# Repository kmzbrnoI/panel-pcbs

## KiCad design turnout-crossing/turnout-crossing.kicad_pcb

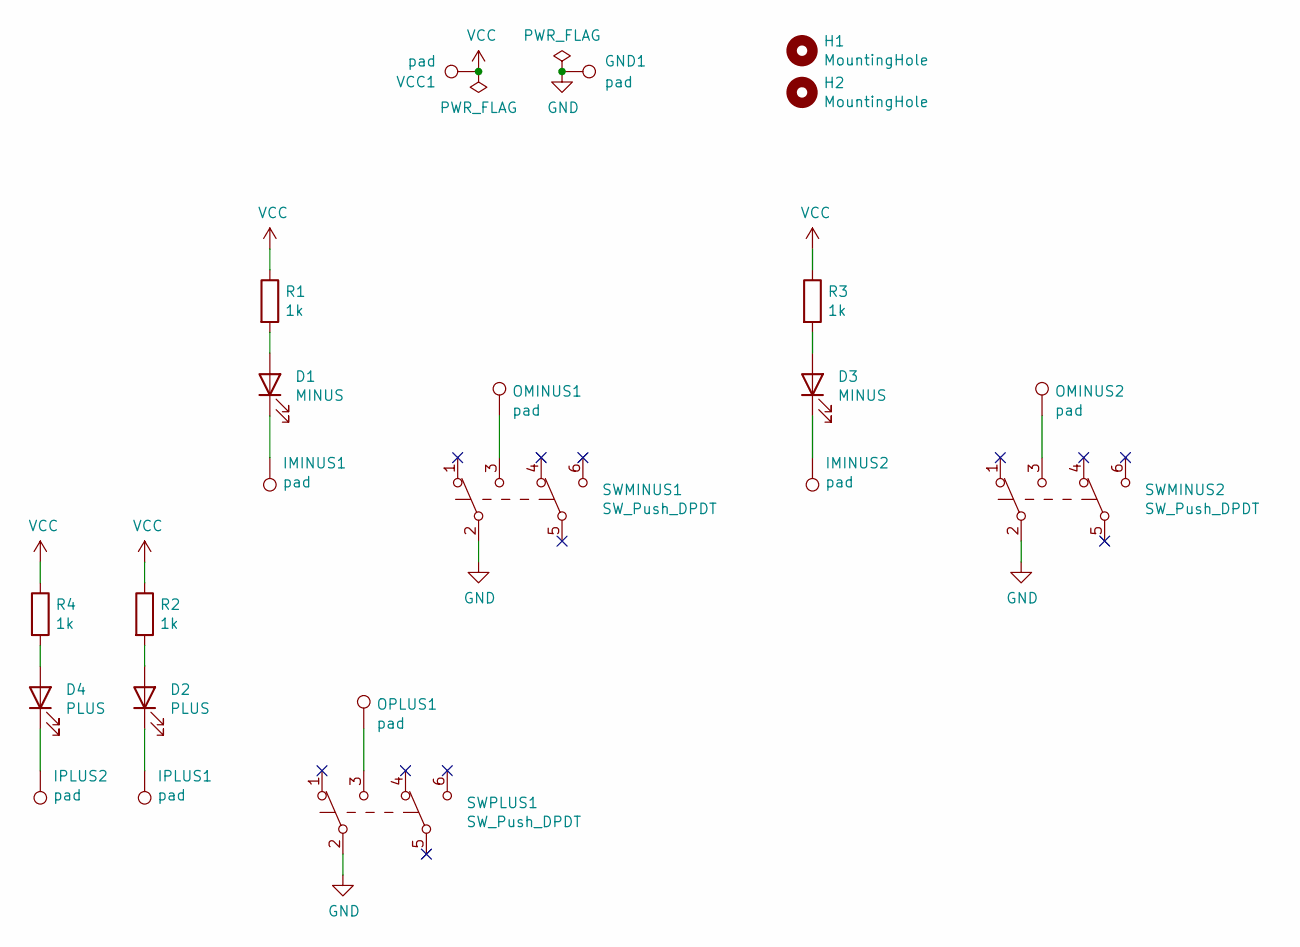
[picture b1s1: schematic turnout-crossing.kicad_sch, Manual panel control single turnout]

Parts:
D1, D3: MINUS; LED_D3.0mm
D2, D4: PLUS; LED_D3.0mm
GND1: pad; Pin_D1.3mm_L11.0mm
H1, H2: MountingHole; MountingHole_3.2mm_M3
IMINUS1, IMINUS2: pad; Pin_D1.3mm_L11.0mm
IPLUS1, IPLUS2: pad; Pin_D1.3mm_L11.0mm
OMINUS1, OMINUS2: pad; Pin_D1.3mm_L11.0mm
OPLUS1: pad; Pin_D1.3mm_L11.0mm
R1, R2, R3, R4: 1k; R_0805_2012Metric_Pad1.20x1.40mm_HandSolder
SWMINUS1, SWMINUS2: SW_Push_DPDT; KLS7
SWPLUS1: SW_Push_DPDT; KLS7
VCC1: pad; Pin_D1.3mm_L11.0mm

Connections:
GND: GND1.1, SWMINUS1.2 (B), SWMINUS2.2 (B), SWPLUS1.2 (B)
unnamed: D1.1 (K), IMINUS1.1
unnamed: D1.2 (A), R1.2
unnamed: D2.1 (K), IPLUS1.1
unnamed: D2.2 (A), R2.2
unnamed: D3.1 (K), IMINUS2.1
unnamed: D3.2 (A), R3.2
unnamed: D4.1 (K), IPLUS2.1
unnamed: D4.2 (A), R4.2
unnamed: OMINUS1.1, SWMINUS1.3 (C)
unnamed: OMINUS2.1, SWMINUS2.3 (C)
unnamed: OPLUS1.1, SWPLUS1.3 (C)
VCC: R1.1, R2.1, R3.1, R4.1, VCC1.1

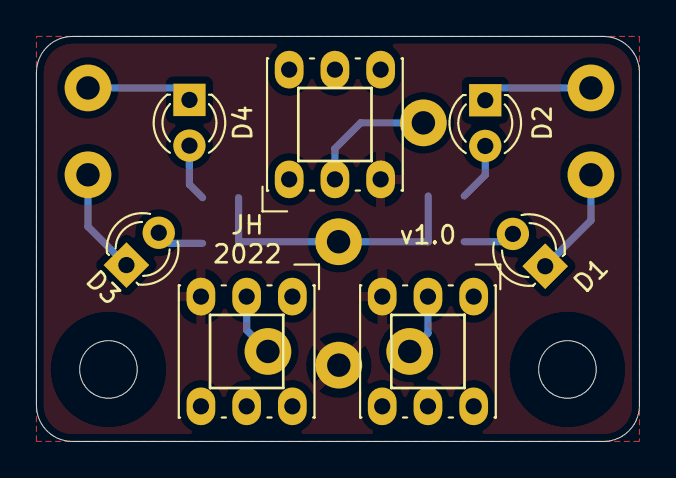
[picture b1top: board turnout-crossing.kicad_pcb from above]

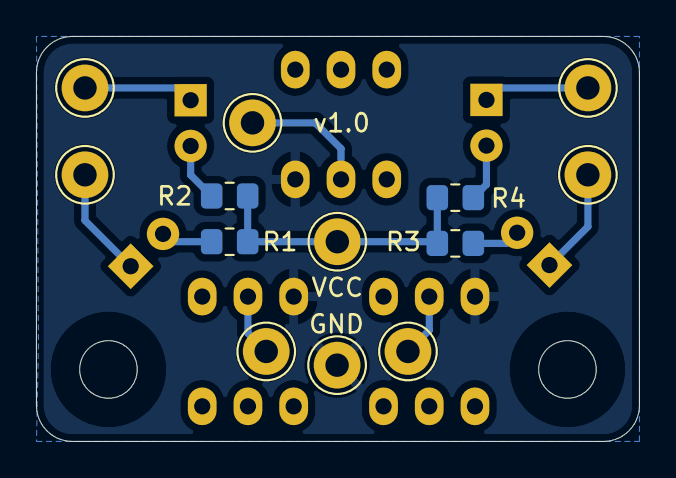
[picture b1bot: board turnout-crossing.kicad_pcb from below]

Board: 2 copper layers, 33.5 x 22.5 mm, 22 parts (13 on the bottom side), 13 nets.

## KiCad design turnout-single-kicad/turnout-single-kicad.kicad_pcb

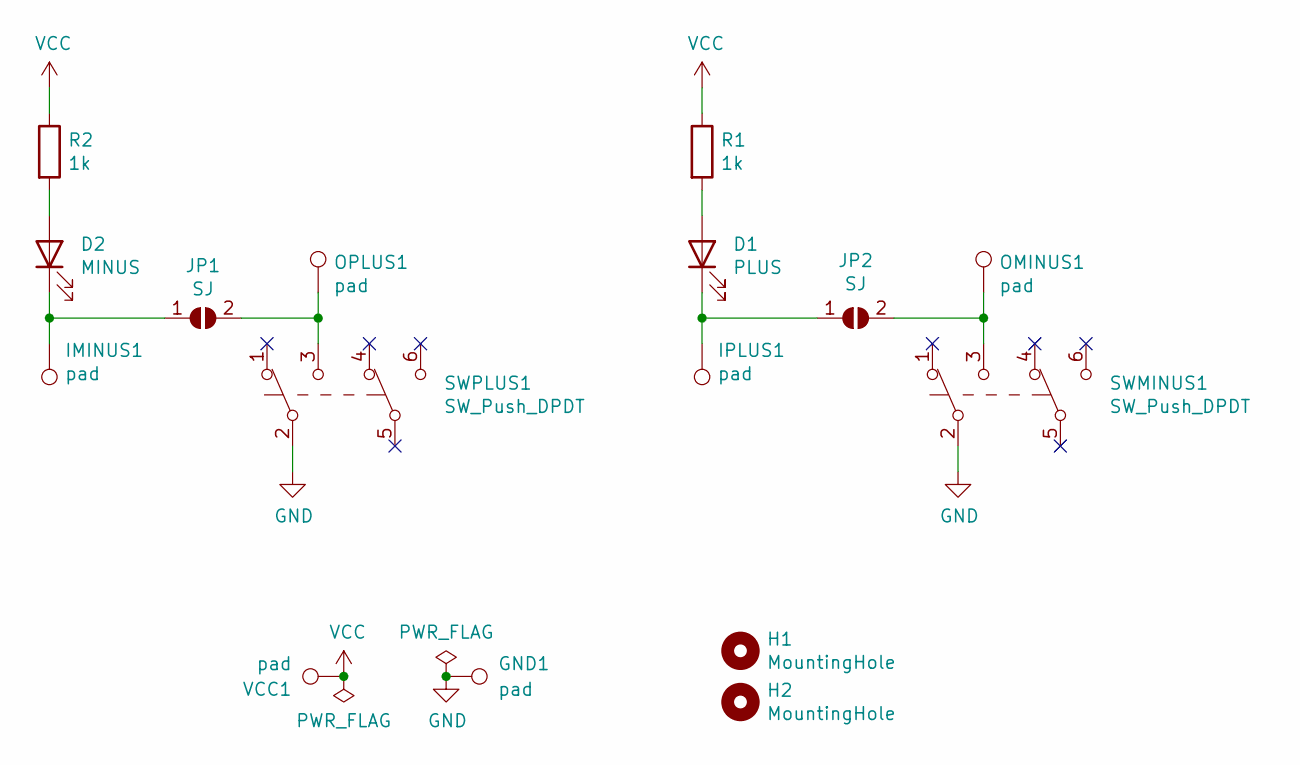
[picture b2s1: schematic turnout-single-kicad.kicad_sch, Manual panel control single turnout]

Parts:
D1: PLUS; LED_D3.0mm
D2: MINUS; LED_D3.0mm
GND1: pad; Pin_D1.3mm_L11.0mm
H1, H2: MountingHole; MountingHole_3.2mm_M3
IMINUS1: pad; Pin_D1.3mm_L11.0mm
IPLUS1: pad; Pin_D1.3mm_L11.0mm
JP1, JP2: SJ; SolderJumper-2_P1.3mm_Open_RoundedPad1.0x1.5mm
OMINUS1: pad; Pin_D1.3mm_L11.0mm
OPLUS1: pad; Pin_D1.3mm_L11.0mm
R1, R2: 1k; R_0805_2012Metric_Pad1.20x1.40mm_HandSolder
SWMINUS1: SW_Push_DPDT; KLS7
SWPLUS1: SW_Push_DPDT; KLS7
VCC1: pad; Pin_D1.3mm_L11.0mm

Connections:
GND: GND1.1, SWMINUS1.2 (B), SWPLUS1.2 (B)
unnamed: D1.1 (K), IPLUS1.1, JP2.1 (A)
unnamed: D1.2 (A), R1.2
unnamed: D2.1 (K), IMINUS1.1, JP1.1 (A)
unnamed: D2.2 (A), R2.2
unnamed: JP1.2 (B), OPLUS1.1, SWPLUS1.3 (C)
unnamed: JP2.2 (B), OMINUS1.1, SWMINUS1.3 (C)
VCC: R1.1, R2.1, VCC1.1

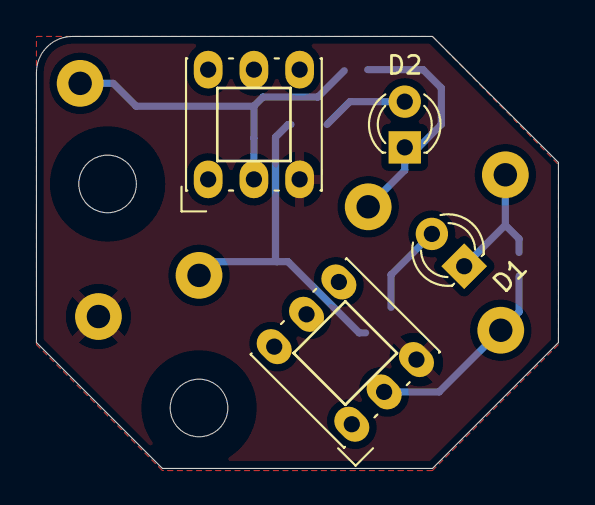
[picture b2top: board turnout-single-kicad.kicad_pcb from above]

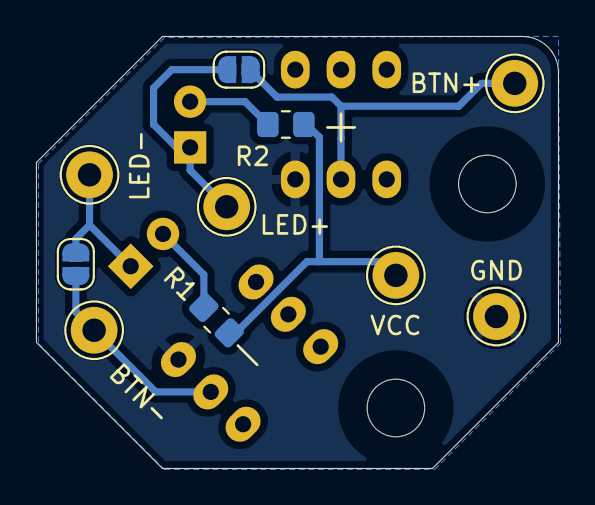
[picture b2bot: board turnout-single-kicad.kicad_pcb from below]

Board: 2 copper layers, 29.0 x 24.0 mm, 16 parts (10 on the bottom side), 8 nets.

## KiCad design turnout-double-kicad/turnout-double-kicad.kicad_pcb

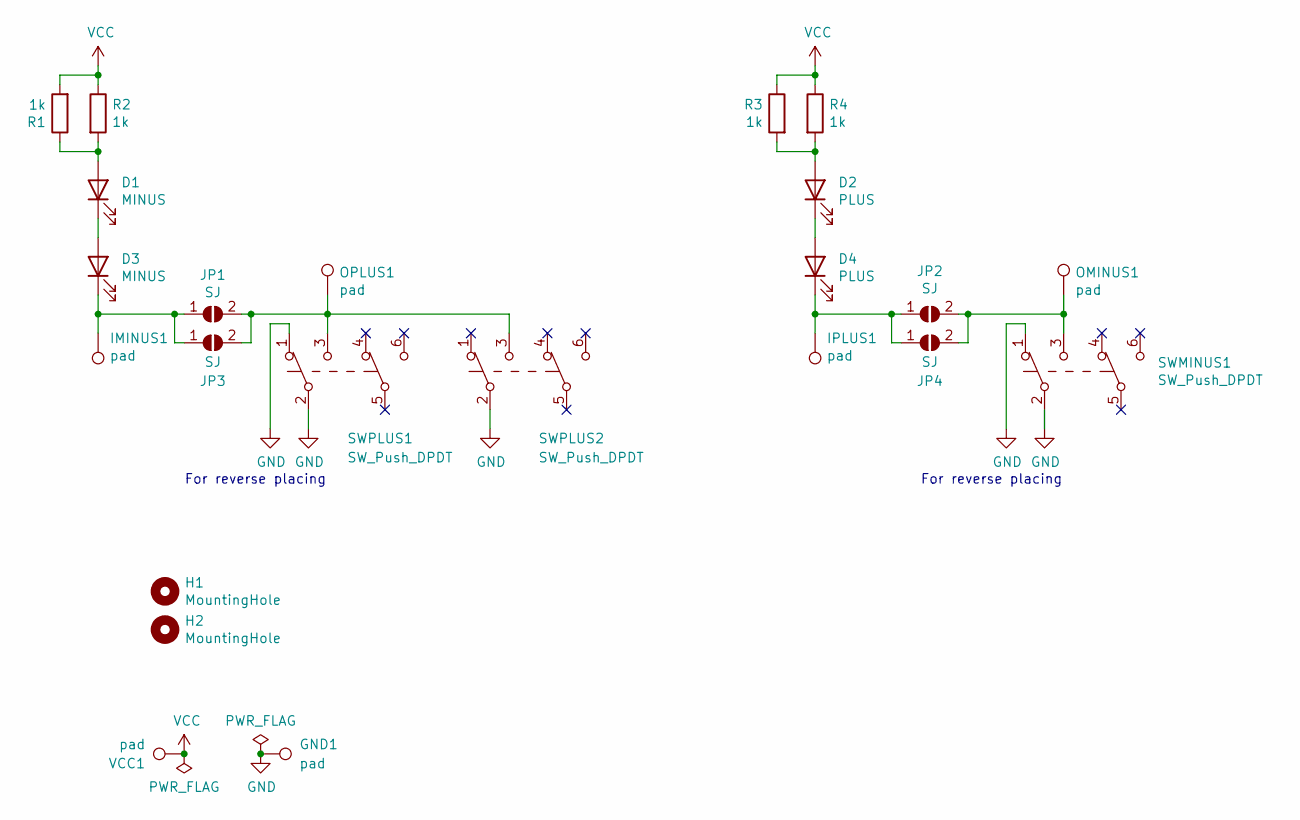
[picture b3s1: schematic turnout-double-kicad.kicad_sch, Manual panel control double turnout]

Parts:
D1, D3: MINUS; LED_D3.0mm
D2, D4: PLUS; LED_D3.0mm
GND1: pad; Pin_D1.3mm_L11.0mm
H1, H2: MountingHole; MountingHole_3.2mm_M3
IMINUS1: pad; Pin_D1.3mm_L11.0mm
IPLUS1: pad; Pin_D1.3mm_L11.0mm
JP1, JP2, JP3, JP4: SJ; SolderJumper-2_P1.3mm_Open_RoundedPad1.0x1.5mm
OMINUS1: pad; Pin_D1.3mm_L11.0mm
OPLUS1: pad; Pin_D1.3mm_L11.0mm
R1, R2, R3, R4: 1k; R_0805_2012Metric_Pad1.20x1.40mm_HandSolder
SWMINUS1: SW_Push_DPDT; KLS7
SWPLUS1, SWPLUS2: SW_Push_DPDT; KLS7
VCC1: pad; Pin_D1.3mm_L11.0mm

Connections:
GND: GND1.1, SWMINUS1.1 (A), SWMINUS1.2 (B), SWPLUS1.1 (A), SWPLUS1.2 (B), SWPLUS2.2 (B)
unnamed: D1.1 (K), D3.2 (A)
unnamed: D1.2 (A), R1.1, R2.2
unnamed: D2.1 (K), D4.2 (A)
unnamed: D2.2 (A), R3.2, R4.2
unnamed: D3.1 (K), IMINUS1.1, JP1.1 (A), JP3.1 (A)
unnamed: D4.1 (K), IPLUS1.1, JP2.1 (A), JP4.1 (A)
unnamed: JP1.2 (B), JP3.2 (B), OPLUS1.1, SWPLUS1.3 (C), SWPLUS2.3 (C)
unnamed: JP2.2 (B), JP4.2 (B), OMINUS1.1, SWMINUS1.3 (C)
VCC: R1.2, R2.1, R3.1, R4.1, VCC1.1

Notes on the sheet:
For reverse placing

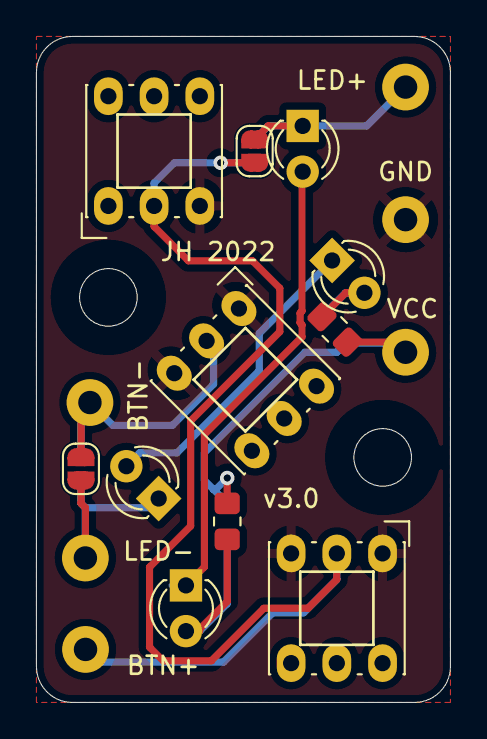
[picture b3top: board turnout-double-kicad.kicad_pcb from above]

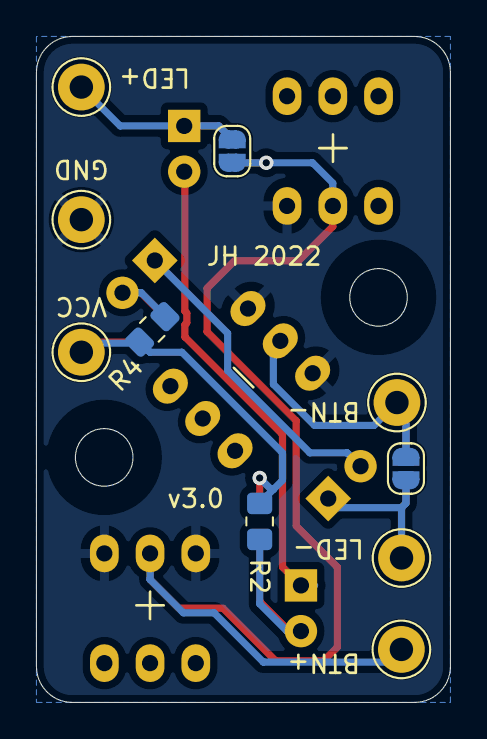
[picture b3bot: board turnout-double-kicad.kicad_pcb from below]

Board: 2 copper layers, 23.0 x 37.0 mm, 23 parts (10 on the bottom side), 10 nets.

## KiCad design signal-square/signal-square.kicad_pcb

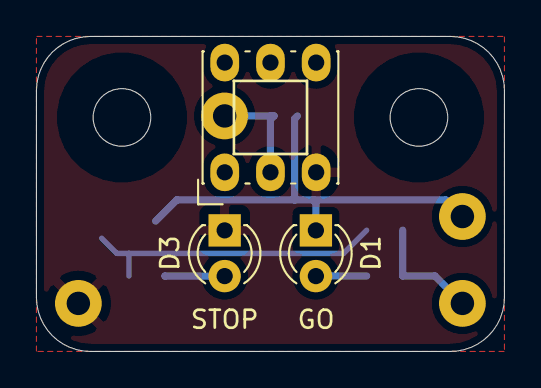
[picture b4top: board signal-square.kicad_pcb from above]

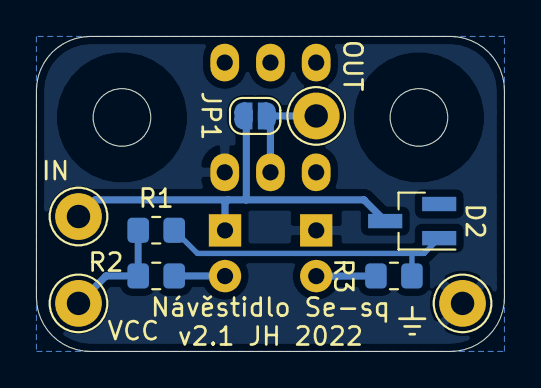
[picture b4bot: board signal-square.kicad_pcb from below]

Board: 2 copper layers, 26.0 x 17.5 mm, 14 parts (9 on the bottom side), 7 nets.

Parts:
CGND1: pad; Pin_D1.3mm_L11.0mm
CINPUT1: pad; Pin_D1.3mm_L11.0mm
COUTPUT1: pad; Pin_D1.3mm_L11.0mm
CVCC1: pad; Pin_D1.3mm_L11.0mm
D1: GO; LED_D3.0mm
D2: BAT54W; SOT-23_Handsoldering
D3: STOP; LED_D3.0mm
H1, H2: MountingHole; MountingHole_3.2mm_M3
JP1: SolderJumper_2_Open; SolderJumper-2_P1.3mm_Open_RoundedPad1.0x1.5mm
R1, R2, R3: 1k; R_0805_2012Metric_Pad1.20x1.40mm_HandSolder
SW1: SW_Push_DPDT; KLS7

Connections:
GND: CGND1.1, D3.1, SW1.2
unnamed: CINPUT1.1, D1.1, D2.3, JP1.1
unnamed: COUTPUT1.1, JP1.2, SW1.3
unnamed: D1.2, R1.2
unnamed: D2.1, R2.2, R3.1
unnamed: D3.2, R3.2
VCC: CVCC1.1, R1.1, R2.1

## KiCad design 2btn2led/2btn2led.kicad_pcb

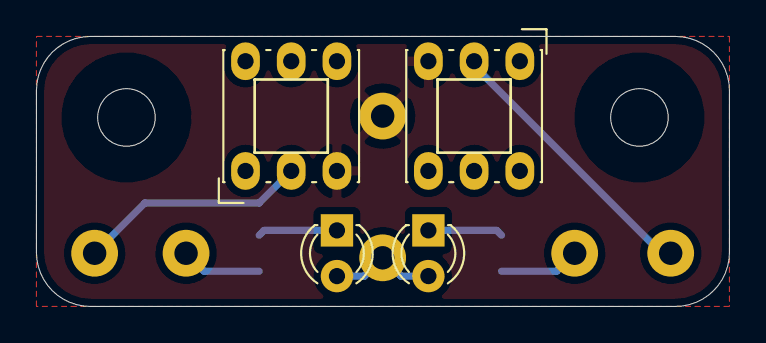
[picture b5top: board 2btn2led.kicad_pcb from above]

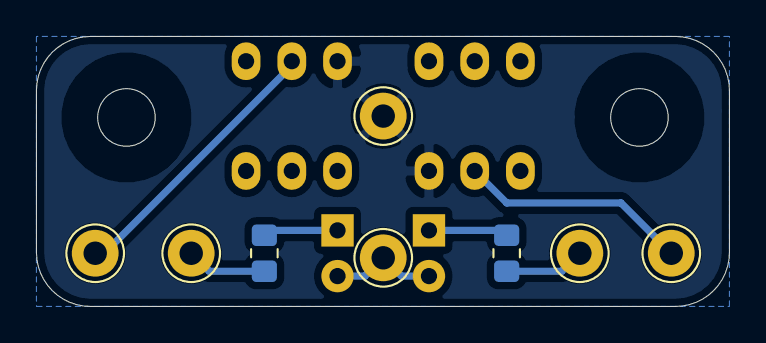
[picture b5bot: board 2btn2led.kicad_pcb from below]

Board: 2 copper layers, 38.5 x 15.0 mm, 14 parts (8 on the bottom side), 8 nets.

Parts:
C1, C2: pad; Pin_D1.3mm_L11.0mm
CINPUT1, CINPUT2: pad; Pin_D1.3mm_L11.0mm
COUTPUT1, COUTPUT2: pad; Pin_D1.3mm_L11.0mm
D1, D2: LED; LED_D3.0mm
H1, H2: MountingHole; MountingHole_3.2mm_M3
R1, R2: 1k; R_0805_2012Metric_Pad1.20x1.40mm_HandSolder
SW1, SW2: SW_Push_DPDT; KLS7

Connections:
GND: C2.1, SW1.2, SW2.2
unnamed: CINPUT1.1, R1.2
unnamed: CINPUT2.1, R2.2
unnamed: COUTPUT1.1, SW1.3
unnamed: COUTPUT2.1, SW2.3
unnamed: D1.1, R1.1
unnamed: D2.1, R2.1
VCC: C1.1, D1.2, D2.2

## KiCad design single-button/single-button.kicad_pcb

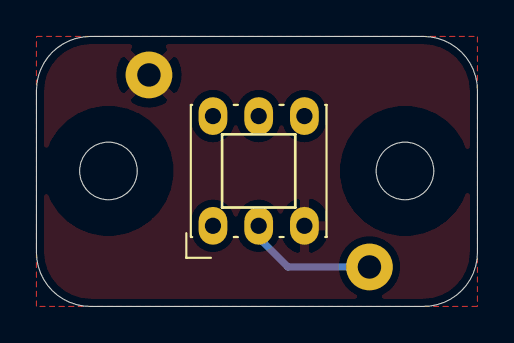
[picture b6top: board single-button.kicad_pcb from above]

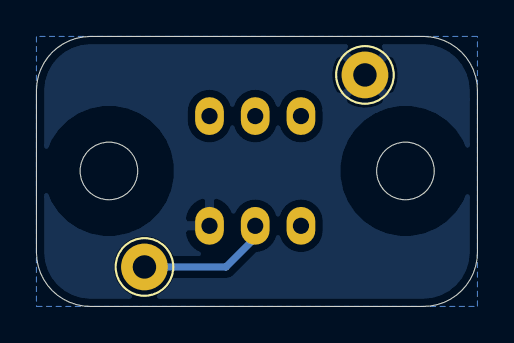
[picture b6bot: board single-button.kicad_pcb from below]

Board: 2 copper layers, 24.5 x 15.0 mm, 5 parts (2 on the bottom side), 2 nets.

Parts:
CGND1: pad; Pin_D1.3mm_L11.0mm
CSIG1: pad; Pin_D1.3mm_L11.0mm
H1, H2: MountingHole; MountingHole_3.2mm_M3
SW1: SW_Push_DPDT; KLS7

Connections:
GND: CGND1.1, SW1.2
unnamed: CSIG1.1, SW1.3

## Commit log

2021-11-06 Add Eagle .gitignore.
2021-11-06 Add all PCBs.
2021-11-06 Add Se signal PCB.
2021-11-07 gitignore kicad files.
2021-11-07 Add signal-1btn schematics in kicad.
2021-11-07 Add KLS7 switch library
2021-11-07 Update kicad .gitignore.
2021-11-07 Add signal-1btn-kicad PCB.
2021-11-07 Add Makefile for panelization & production data.
2021-11-07 Add texts, use 2×5 panel.
2021-11-09 Import signal to turnout-single.
2021-11-09 Add turnout schematics.
2021-11-09 Add turnout-single pcb.
2021-11-09 Add solder-jumpers for connecting inputs & outputs.
2021-11-09 Add description as plain texts.
2021-11-09 Remove Cu from around mounting holes.
2021-11-10 Use mounting holes without Cu.
2021-11-10 Add single button pcb.
2021-11-10 Add double-turnout PCB.
2021-11-10 Change panelization to mousebites.
2021-11-10 single-button: add nice panel parameters.
2021-11-10 Single-button: add pads to other side to make mounting easier.
2021-11-23 Add signal-square PCB.
2021-11-24 Turnout-double: add mounting holes clearance.
2021-11-28 Update turnout-single.
2021-11-28 Use negative offset in mousebites panelization.
2021-12-16 Fix BAT54 package (SOT23).
2021-12-16 Fix package.
2021-12-16 Signal: switch diodes.
2021-12-16 Turnout-double: allow both side placement.
2021-12-17 Turnout-double: dubplicate parts.
    To allow mirror placement on panel.
2021-12-17 Add 2btn2leds pcb.
2022-01-12 Add missing wire.
2022-01-27 turnout-double: migrate to KiCad 6.
2022-01-27 turnout-double: add wires for reversed placing.
2022-01-27 turnout-double: add author & version to silkscreen.
2022-01-27 turnout-single: update to KiCad 6.
2022-01-27 Add turnout-crossing.
